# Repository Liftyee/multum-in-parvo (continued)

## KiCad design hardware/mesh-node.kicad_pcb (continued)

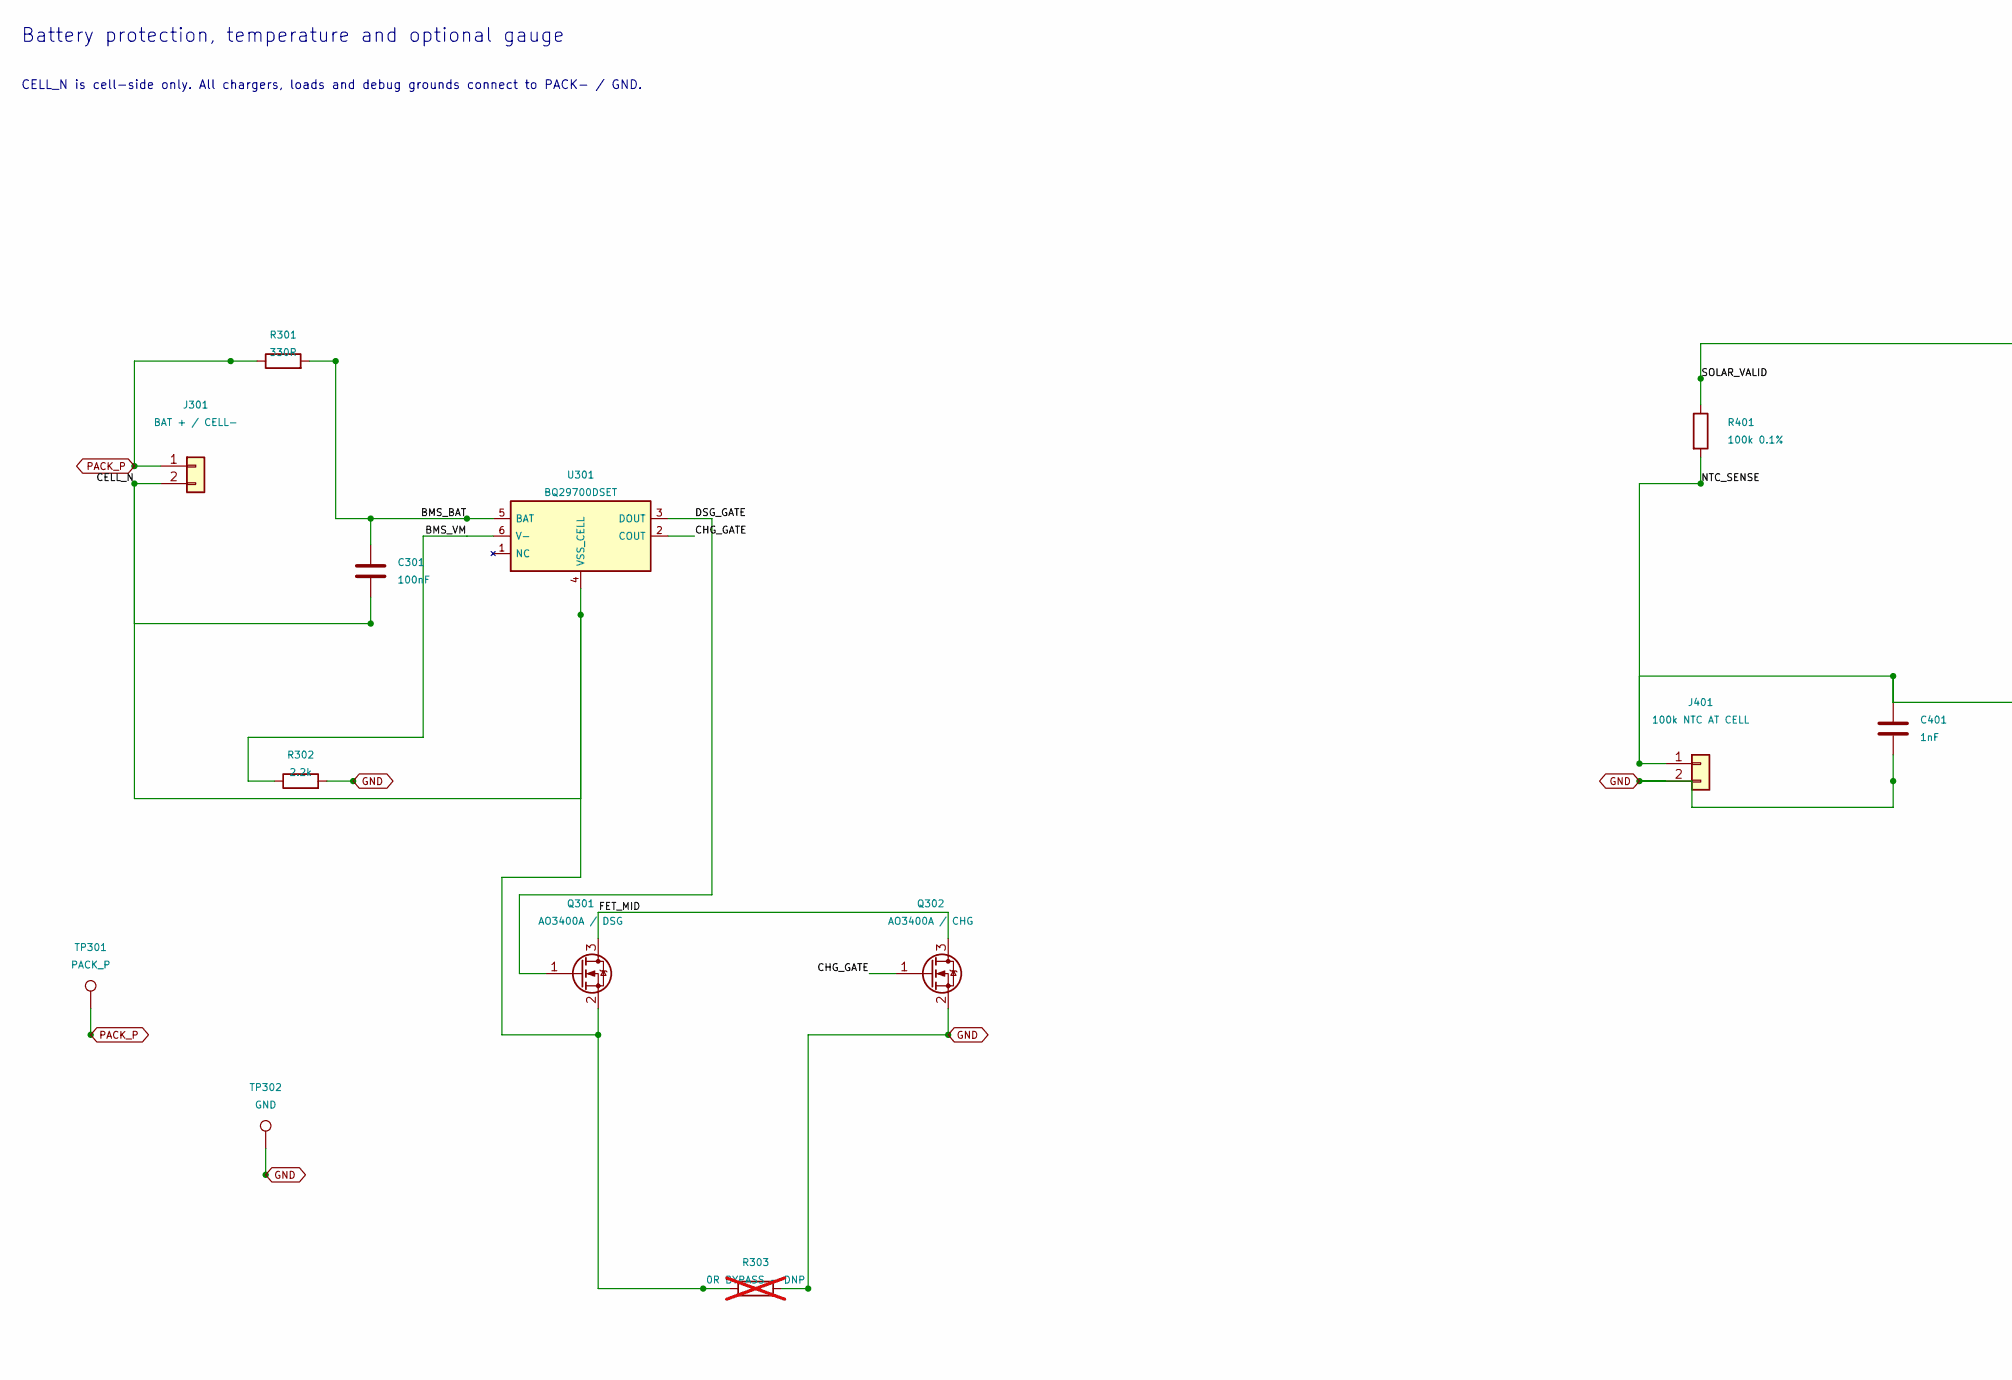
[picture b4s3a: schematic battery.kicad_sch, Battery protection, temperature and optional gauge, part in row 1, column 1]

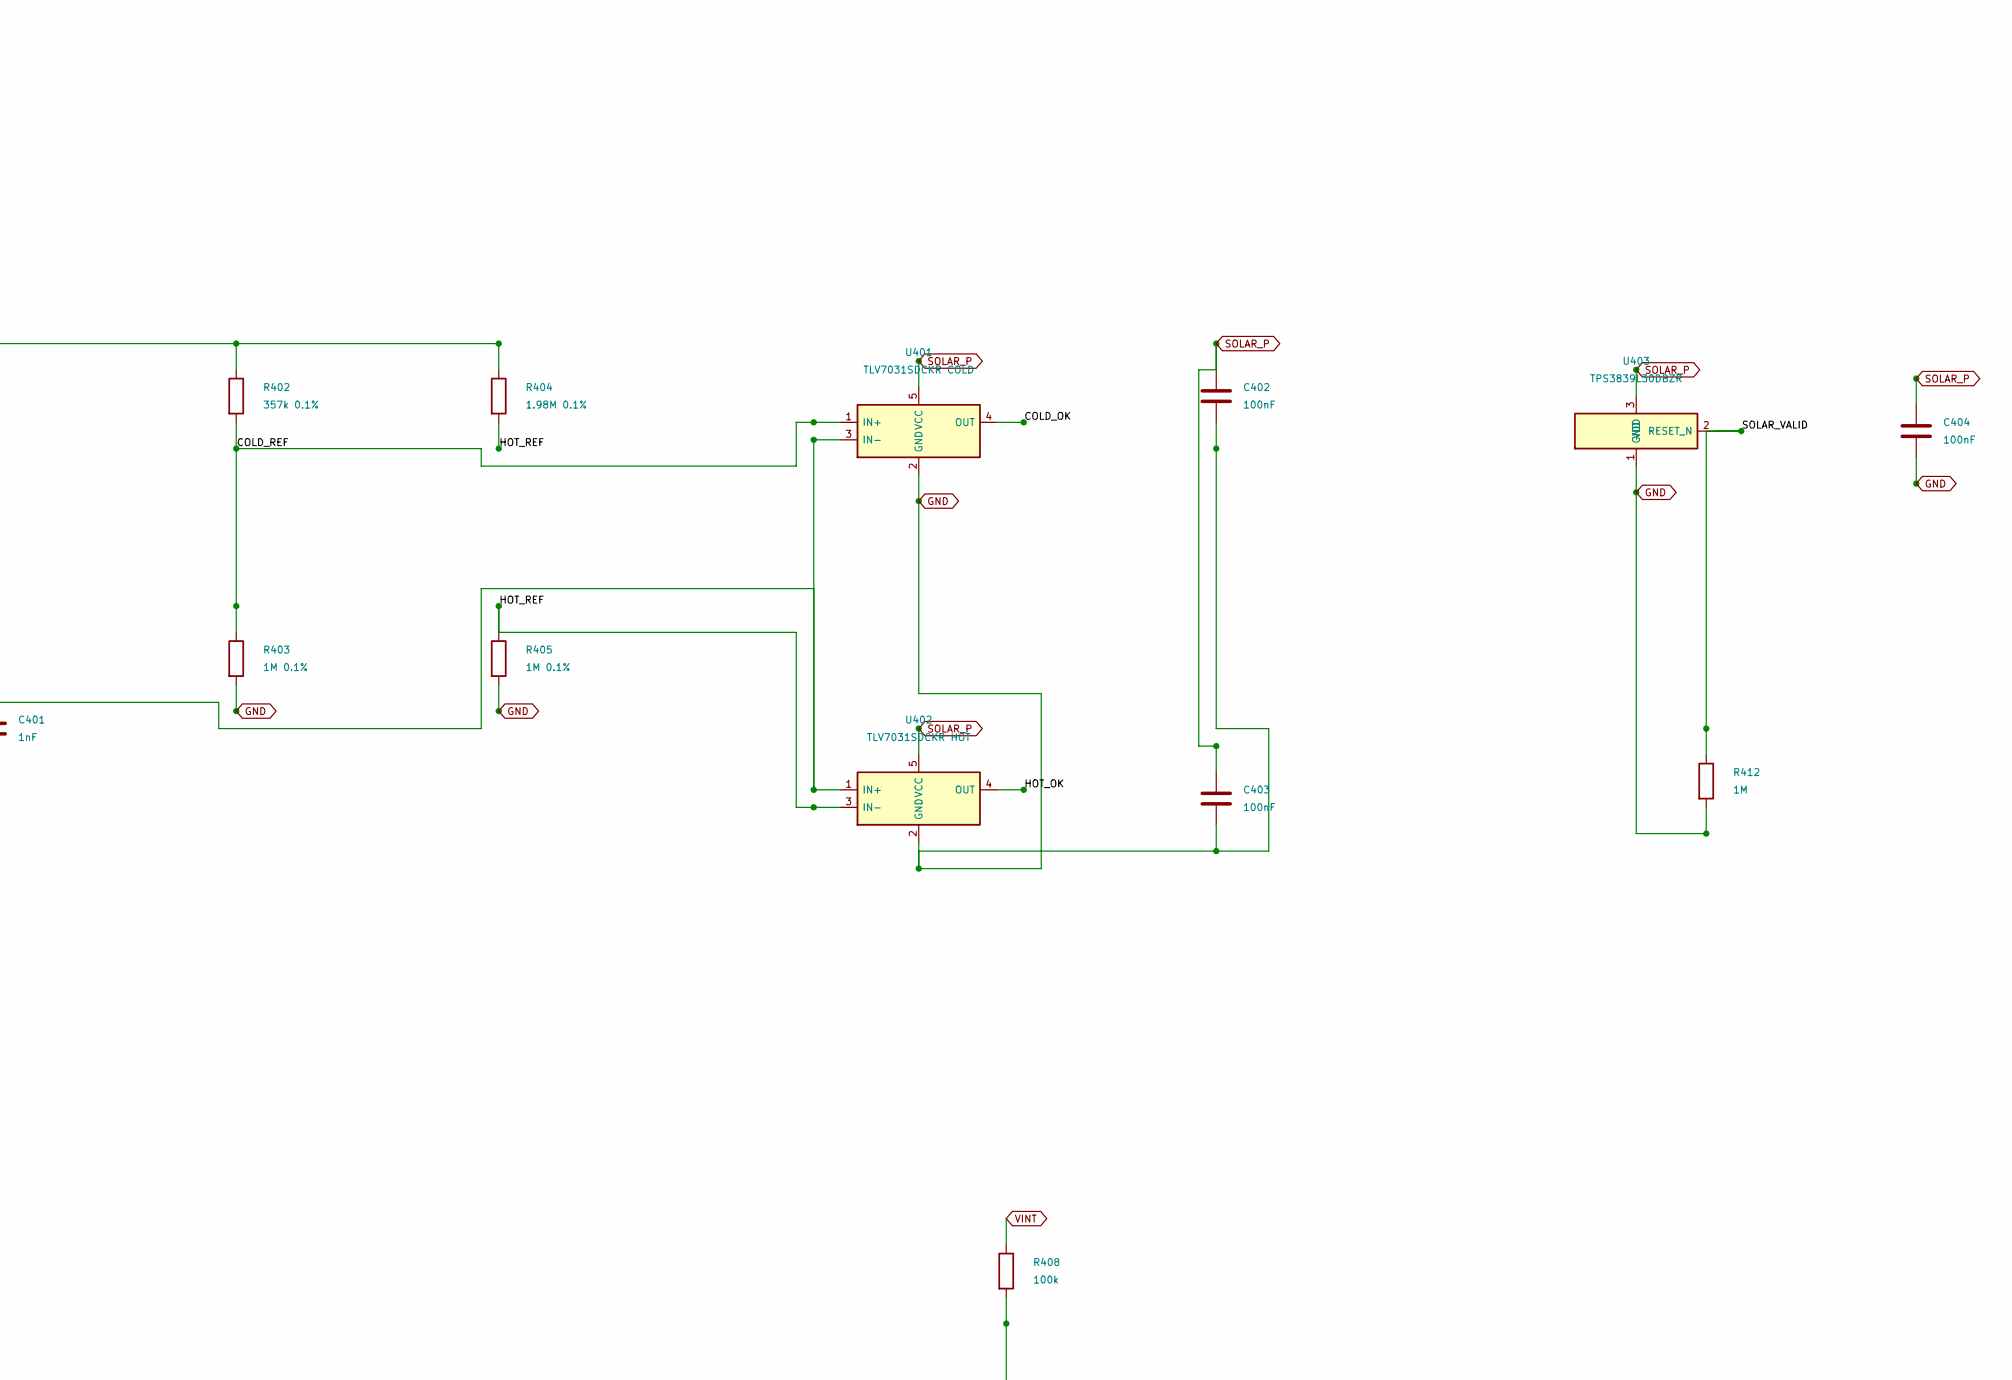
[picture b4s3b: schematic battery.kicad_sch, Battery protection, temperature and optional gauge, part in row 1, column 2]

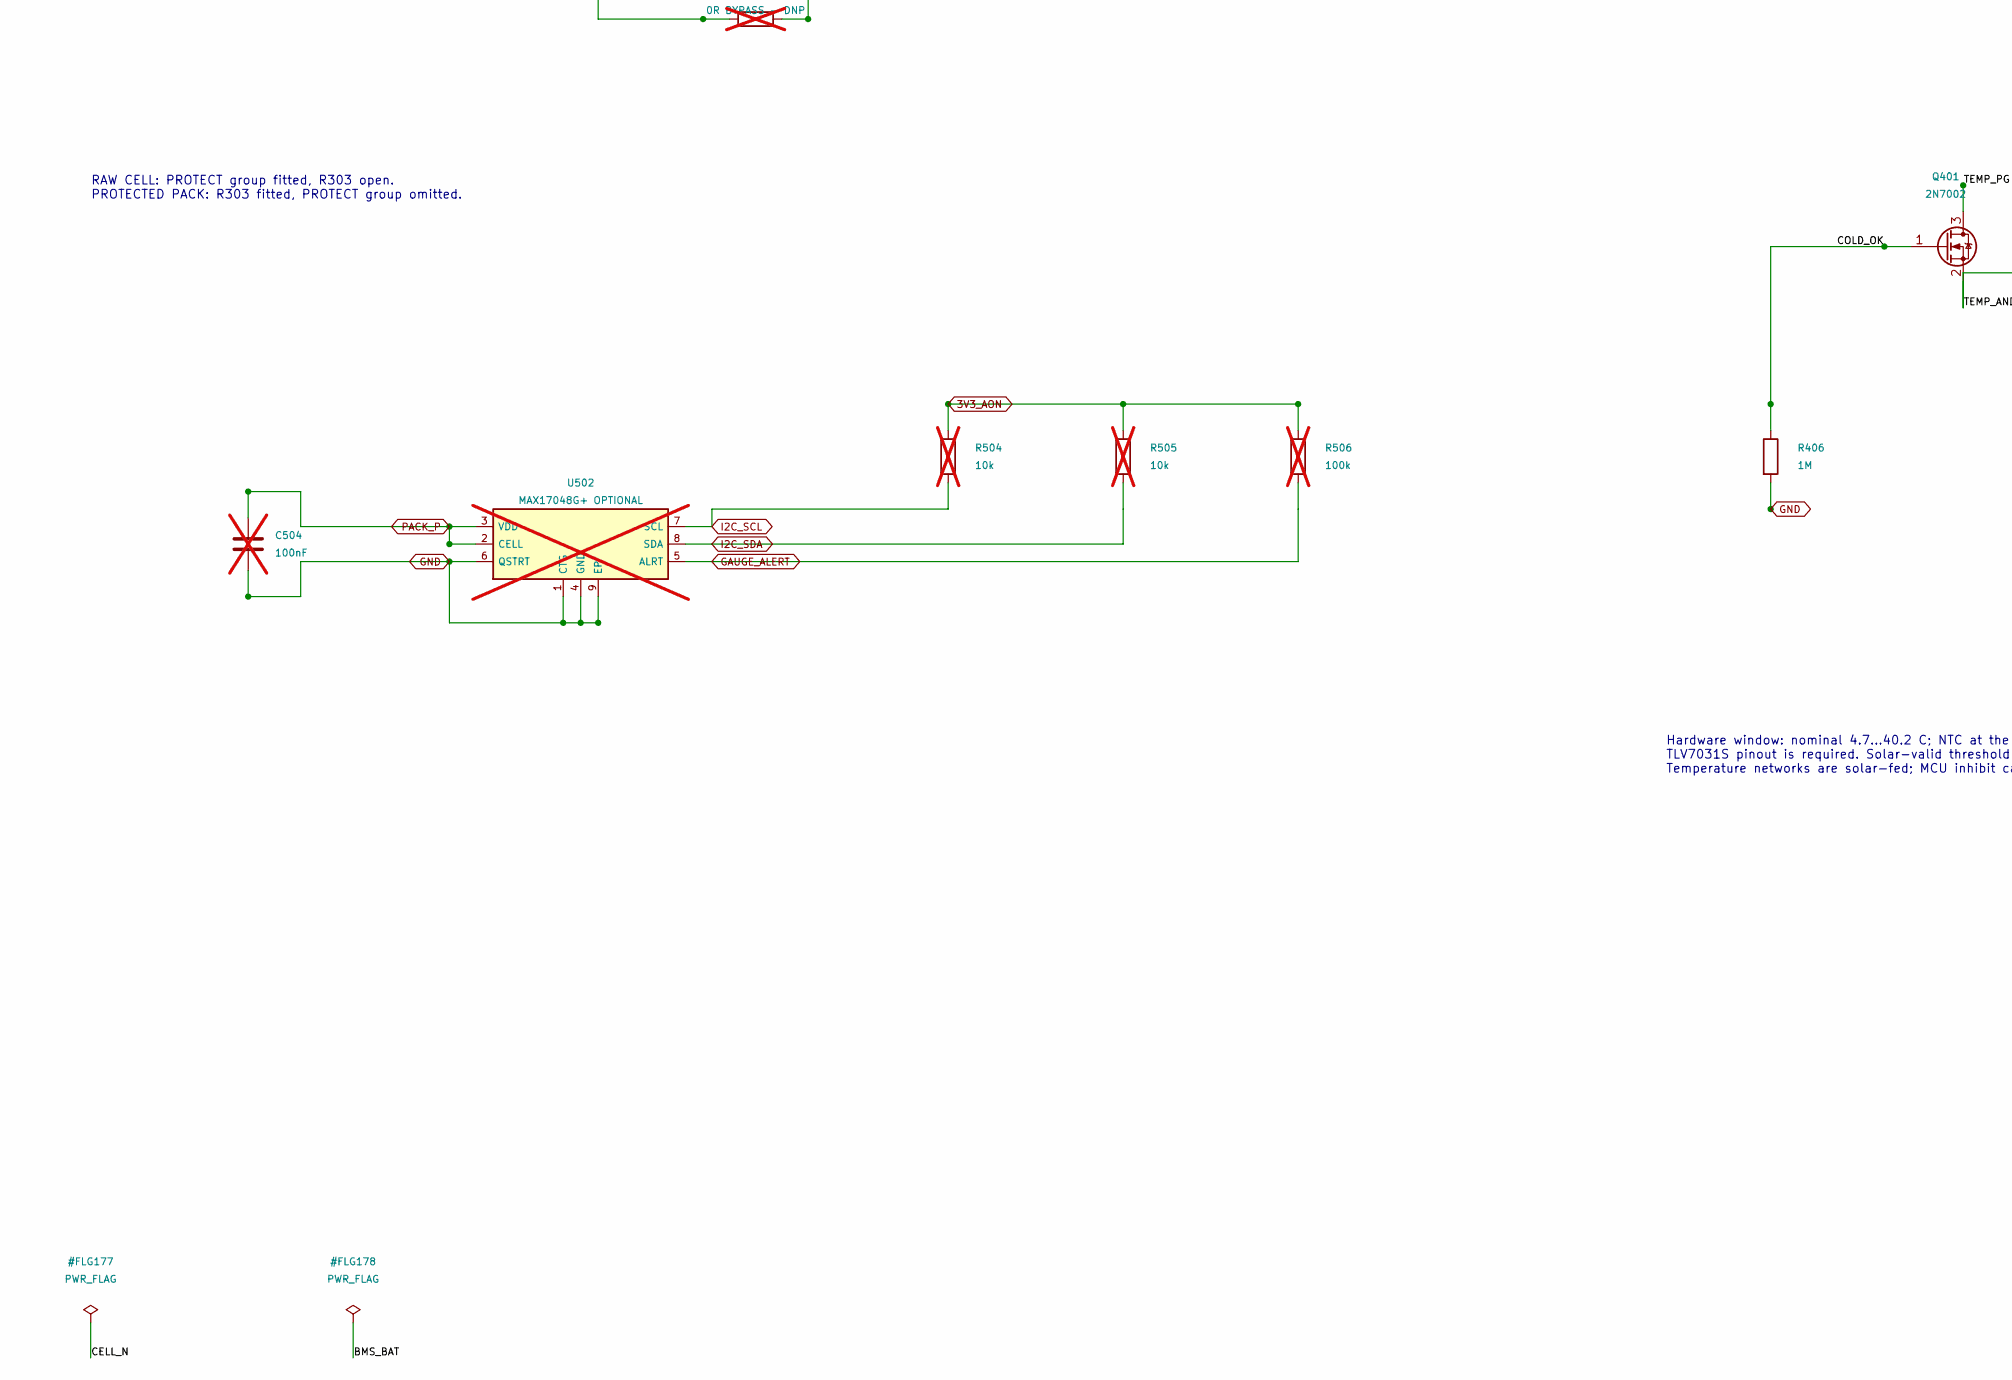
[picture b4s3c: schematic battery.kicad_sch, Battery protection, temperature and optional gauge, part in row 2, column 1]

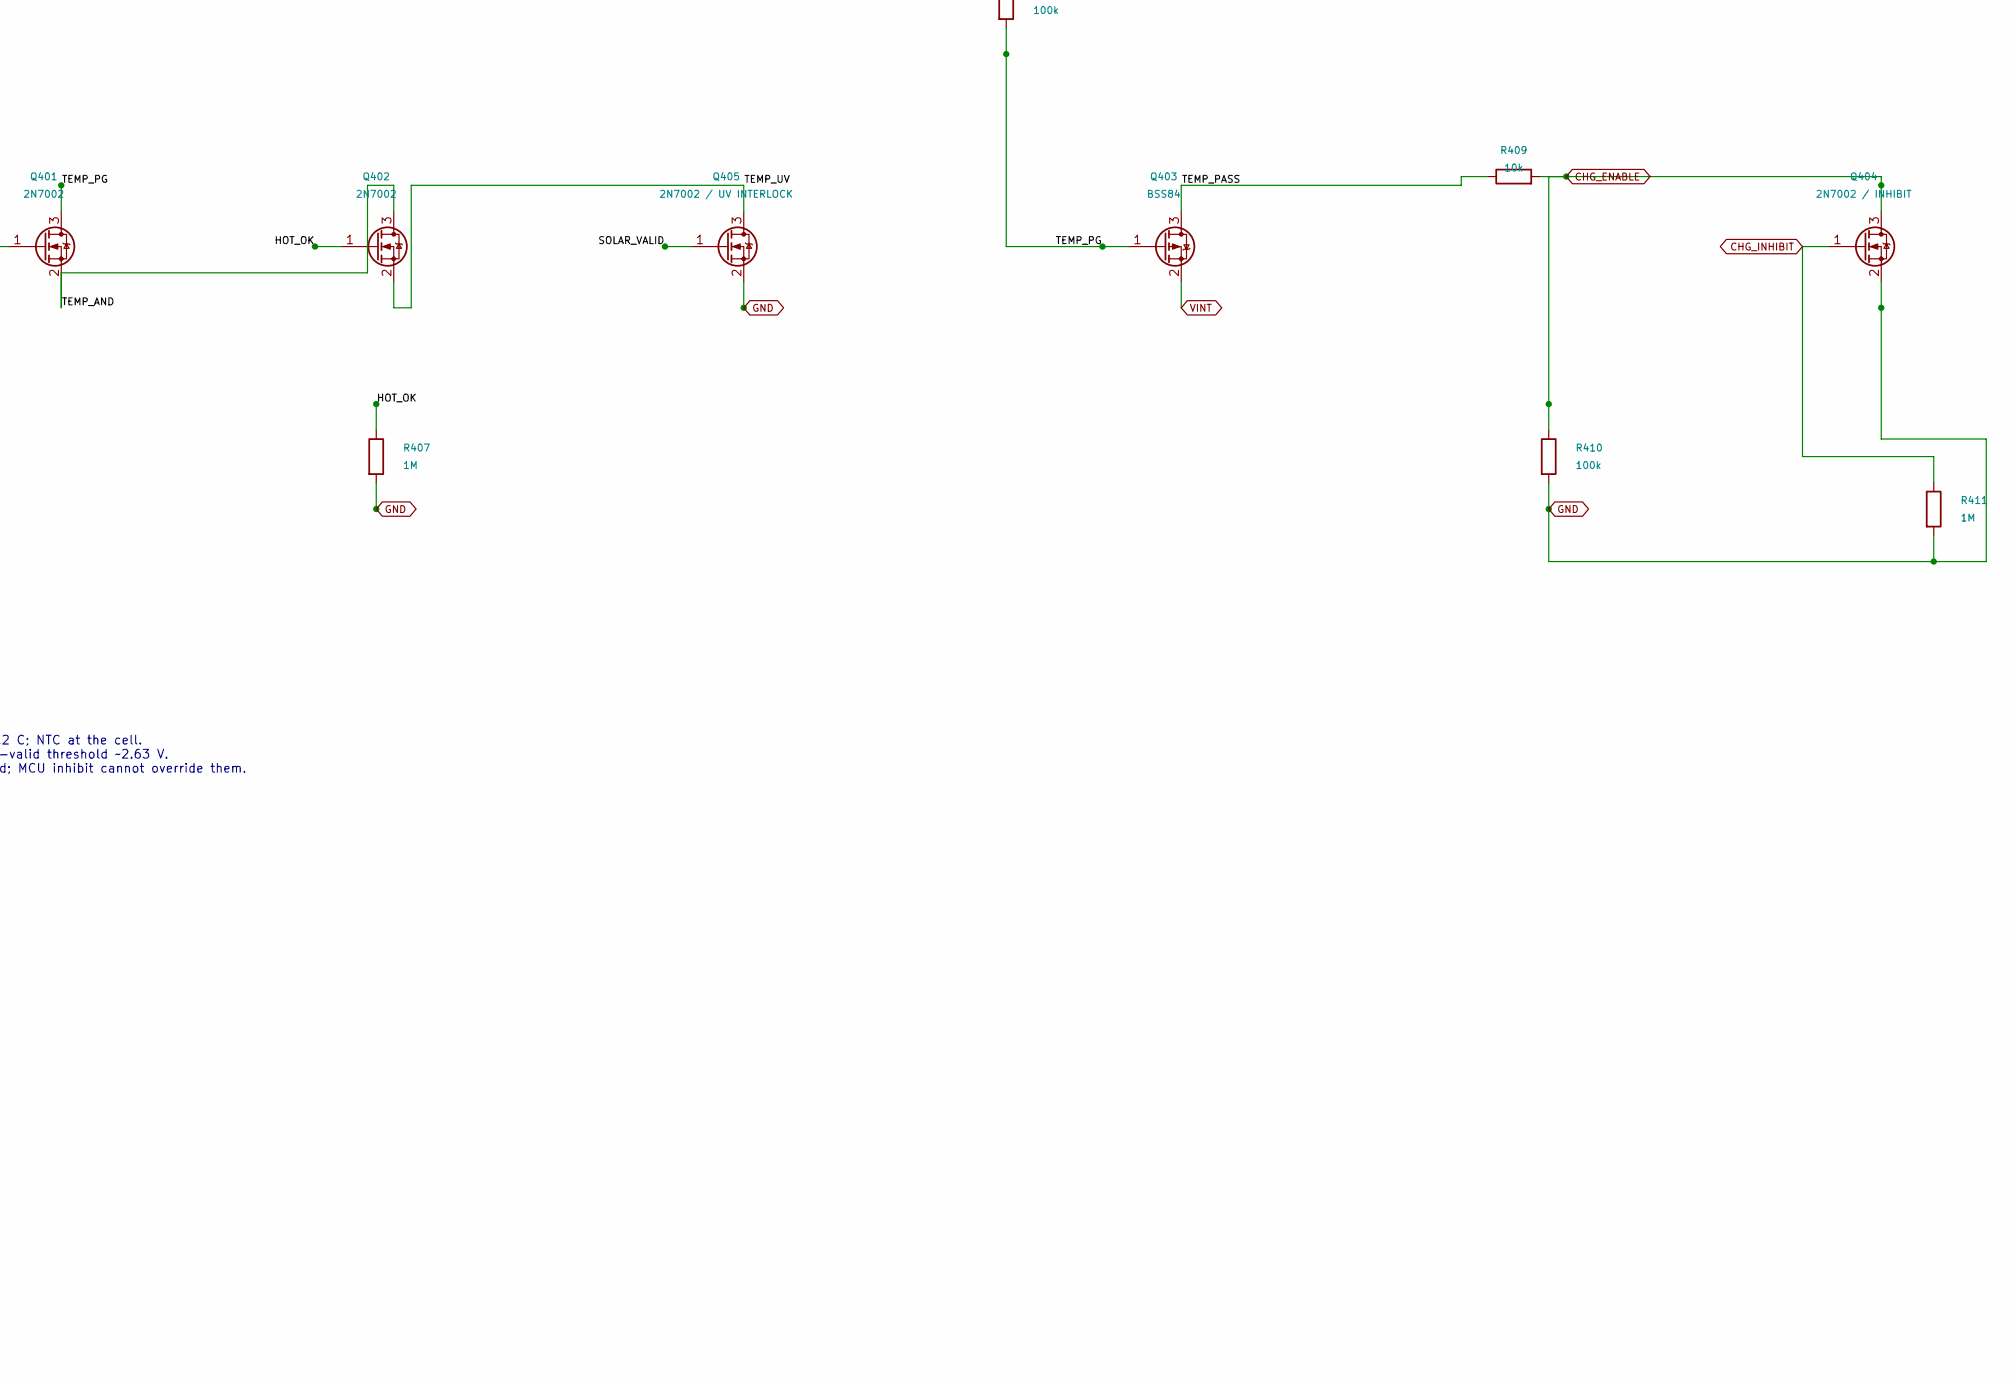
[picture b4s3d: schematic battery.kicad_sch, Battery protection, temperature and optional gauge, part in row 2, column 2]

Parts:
C301, C402, C403, C404: 100nF; C0603; MPN 100nF
C401: 1nF; C0603; MPN 1nF
C504: 100nF; C0603; MPN 100nF; not fitted
J301: BAT + / CELL-; JST_PH_2; MPN B2B-PH-K-S(LF)(SN)
J401: 100k NTC AT CELL; Header1x2; MPN External NTC NCP18WF104F12RB mounted on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
Q301: AO3400A / DSG; SOT23; MPN AO3400A
Q302: AO3400A / CHG; SOT23; MPN AO3400A
Q401, Q402: 2N7002; SOT23; MPN 2N7002
Q403: BSS84; SOT23; MPN BSS84
Q404: 2N7002 / INHIBIT; SOT23; MPN 2N7002 / INHIBIT
Q405: 2N7002 / UV INTERLOCK; SOT23; MPN 2N7002 / UV INTERLOCK
R301: 330R; R0603; MPN 330R
R302: 2.2k; R0603; MPN 2.2k
R303: 0R BYPASS - DNP; R1206; MPN 0R BYPASS - DNP; not fitted
R401: 100k 0.1%; R0603; MPN 100k 0.1%
R402: 357k 0.1%; R0603; MPN 357k 0.1%
R403, R405: 1M 0.1%; R0603; MPN 1M 0.1%
R404: 1.98M 0.1%; R0603; MPN 1.98M 0.1%
R406, R407, R411, R412: 1M; R0603; MPN 1M
R408, R410: 100k; R0603; MPN 100k
R409: 10k; R0603; MPN 10k
R504, R505: 10k; R0603; MPN 10k; not fitted
R506: 100k; R0603; MPN 100k; not fitted
TP301: PACK_P; TestPad; MPN PACK_P
TP302: GND; TestPad; MPN GND
U301: BQ29700DSET; BQ29700_WSON6; MPN BQ29700DSET
U401: TLV7031SDCKR COLD; SC70_5; MPN TLV7031SDCKR COLD
U402: TLV7031SDCKR HOT; SC70_5; MPN TLV7031SDCKR HOT
U403: TPS3839L30DBZR; SOT23; MPN TPS3839L30DBZR
U502: MAX17048G+ OPTIONAL; MAX17048_TDFN8; MPN MAX17048G+; not fitted

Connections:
3V3_AON: R504.1, R505.1, R506.1; also elsewhere on the board
/Battery protection, temperature and optional gauge/BMS_BAT: C301.1, R301.2, U301.5 (BAT)
/Battery protection, temperature and optional gauge/BMS_VM: R302.1, U301.6 (V-)
/Battery protection, temperature and optional gauge/CELL_N: C301.2, J301.2, Q301.2 (S), R303.1, U301.4 (VSS_CELL)
/Battery protection, temperature and optional gauge/CHG_GATE: Q302.1 (G), U301.2 (COUT)
/Battery protection, temperature and optional gauge/COLD_OK: Q401.1 (G), R406.1, U401.4 (OUT)
/Battery protection, temperature and optional gauge/COLD_REF: R402.2, R403.1, U401.1 (IN+)
/Battery protection, temperature and optional gauge/DSG_GATE: Q301.1 (G), U301.3 (DOUT)
/Battery protection, temperature and optional gauge/FET_MID: Q301.3 (D), Q302.3 (D)
/Battery protection, temperature and optional gauge/HOT_OK: Q402.1 (G), R407.1, U402.4 (OUT)
/Battery protection, temperature and optional gauge/HOT_REF: R404.2, R405.1, U402.3 (IN-)
/Battery protection, temperature and optional gauge/NTC_SENSE: C401.1, J401.1, R401.2, U401.3 (IN-), U402.1 (IN+)
/Battery protection, temperature and optional gauge/SOLAR_VALID: Q405.1 (G), R401.1, R402.1, R404.1, R412.1, U403.2 (RESET_N)
/Battery protection, temperature and optional gauge/TEMP_AND: Q401.2 (S), Q402.3 (D)
/Battery protection, temperature and optional gauge/TEMP_PASS: Q403.3 (D), R409.1
/Battery protection, temperature and optional gauge/TEMP_PG: Q401.3 (D), Q403.1 (G), R408.2
/Battery protection, temperature and optional gauge/TEMP_UV: Q402.2 (S), Q405.3 (D)
CHG_ENABLE: Q404.3 (D), R409.2, R410.1; also elsewhere on the board
CHG_INHIBIT: Q404.1 (G), R411.1; also elsewhere on the board
GAUGE_ALERT: R506.2, U502.5 (ALRT); also elsewhere on the board
GND: C401.2, C402.2, C403.2, C404.2, C504.2, J401.2, Q302.2 (S), Q404.2 (S), Q405.2 (S), R302.2, R303.2, R403.2, R405.2, R406.2, R407.2, R410.2, R411.2, R412.2, TP302.1, U401.2 (GND), U402.2 (GND), U403.1 (GND), U502.1 (CTG), U502.4 (GND), U502.6 (QSTRT), U502.9 (EP); also elsewhere on the board
I2C_SCL: R504.2, U502.7 (SCL); also elsewhere on the board
I2C_SDA: R505.2, U502.8 (SDA); also elsewhere on the board
PACK_P: C504.1, J301.1, R301.1, TP301.1, U502.2 (CELL), U502.3 (VDD); also elsewhere on the board
SOLAR_P: C402.1, C403.1, C404.1, U401.5 (VCC), U402.5 (VCC), U403.3 (VDD); also elsewhere on the board
VINT: Q403.2 (S), R408.1; also elsewhere on the board

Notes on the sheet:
Battery protection, temperature and optional gauge
CELL_N is cell-side only. All chargers, loads and debug grounds connect to PACK- / GND.
RAW CELL: PROTECT group fitted, R303 open. PROTECTED PACK: R303 fitted, PROTECT group omitted.
Hardware window: nominal 4.7...40.2 C; NTC at the cell. TLV7031S pinout is required. Solar-valid threshold ~2.63 V. Temperature networks are solar-fed; MCU inhibit cannot override them.
